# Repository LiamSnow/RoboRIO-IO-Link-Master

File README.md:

# RoboRIO-IO-Link-Master
This repo includes the KiCad project for an 8 port IO-Link master that connects over SPI to the RoboRIO.
For code examples check out [IO-Link C++ Generator](https://github.com/LiamSnow/IO-Link-CPP-Generator) and [Ram Robotics](https://github.com/Ram-Robotics).

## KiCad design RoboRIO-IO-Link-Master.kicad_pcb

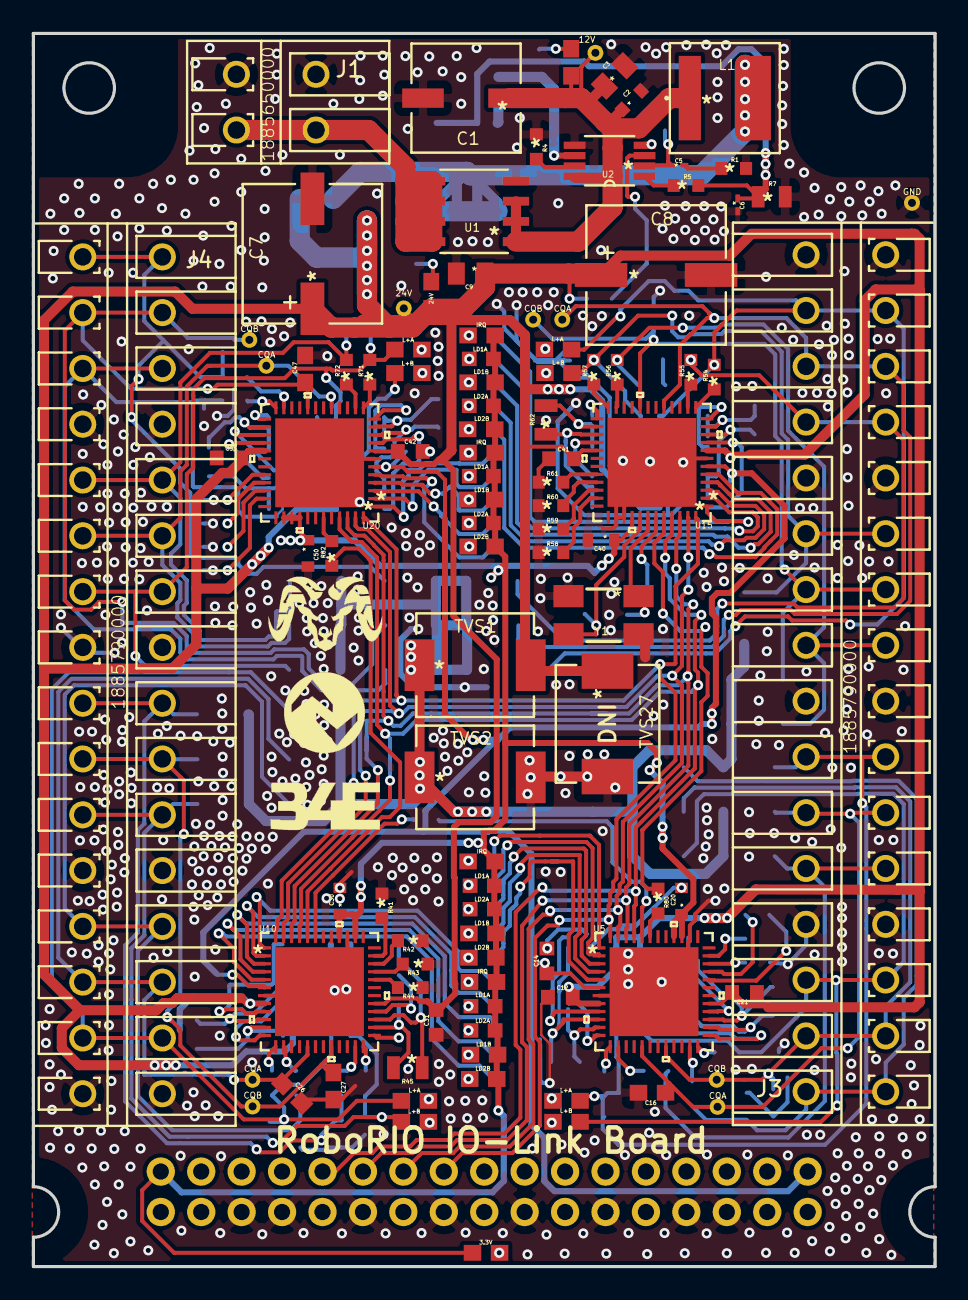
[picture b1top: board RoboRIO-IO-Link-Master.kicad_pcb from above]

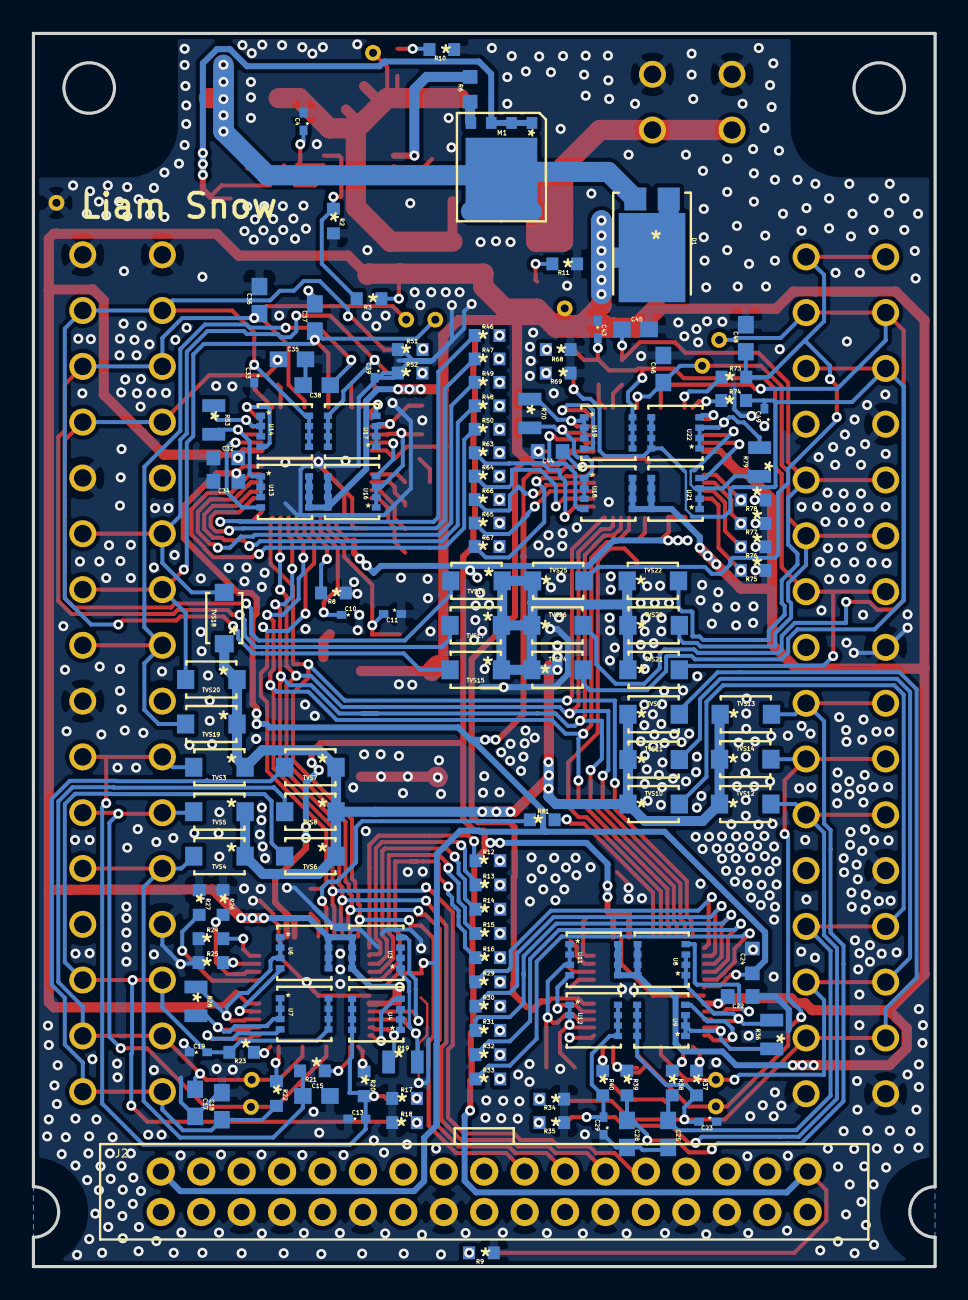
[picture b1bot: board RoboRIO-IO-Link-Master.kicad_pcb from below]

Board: 2 copper layers, 56.6 x 77.5 mm, 232 parts (131 on the bottom side), 168 nets.

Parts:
C1: 100uF-160m; UCL1V101MCL6GS
C2: 100nF-1m; CL10B104KB8NNNC
C3, C9: 10uF; CL21B106KOQNNNE
C4: 1nF; CL05B102KB5NNNC
C5: 22nF; CL03A223KQ3NNNC
C6: 10pF; CL03C100JA3GNNC
C7, C8: 82uF-20m; 35SVPF82M
C10, C11: 5pF; CL05C050CB5NNNC
C12, C14, C21, C22, C24, C31, C32, C34, C41, C42, C44, C51: 1uF; CL10B105MO8NNWC
C13, C19, C23, C29, C33, C39, C43, C49: 0.47uF; CL05A474KP5NNNC
C15, C16, C17, C18, C25, C26, C27, C28, C35, C36, C37, C38, C45, C46, C47, C48: 270pF; CC0603JRNPO9BN271
C20, C30, C40, C50: 0.1uF; CL10B104KB8NNNC
D1: 950mV-10A; FSV10150V
D2: 3.3V; LTSTC191KRKT
D3: 12V; LTSTC191KRKT
D4: 24V; LTSTC191KRKT
D6, D13, D20, D27: IRQ; LTSTC191KFKT
D7, D14, D21, D28: LD1A; LTSTC191TBKT
D8, D15, D22, D29: LD2A; LTSTC191TBKT
D9, D16, D23, D30: LD1B; LTSTC191KGKT
D10, D17, D24, D31: LD2B; LTSTC191KGKT
D11, D18, D25, D32: L+A; LTSTC191KRKT
D12, D19, D26, D33: L+B; LTSTC191KRKT
J1: 1885650000
J2: SFH11-PBPC-D17-ST-BK
J3, J4: 1885790000
L1: 4.7uH-13m; 74439346047
M1: CSD18504Q5A
R1: 4.42k; RC0603FR074K42L
R2, R80, R81, R82: 1k; RC0603FR071KL
R3: 18.2k; RC0603FR0718K2L
R4: 26.1k; RC0603FR0726K1L
R5, R20, R21, R22, R23, R37, R38, R39, R40, R54, R55, R56, R57, R71, R72, R73, R74: 100; RC0603JR07100RL
R6: 0; CRCW06030000Z0EBC
R7: 6m; PMR10EZPFU6L00
R8, R10, R24, R25, R26, R27, R41, R42, R43, R44, R58, R59, R60, R61, R75, R76, R77, R78: 10k; RC0603FR0710KL
R9: 1.5k; RC0603JR071K5L
R11: 22k; RC0603JR0722KL
R12, R13, R14, R15, R16, R29, R30, R31, R32, R33, R46, R47, R48, R49, R50, R63, R64, R65, R66, R67: 820; RC0603FR07820RL
R17, R18, R34, R35, R51, R52, R68, R69: 6.8k; RC0603FR076K8L
R19, R28, R36, R45, R53, R62, R70, R79: .012; KRL1220E-M-R012-F-T5
TP1: GND; TestPointFootprint
TP2: 12V; TestPointFootprint
TP3: 24V; TestPointFootprint
TP7, TP18, TP29, TP40: CQA; TestPointFootprint
TP8, TP19, TP30, TP41: CQB; TestPointFootprint
TVS1: SM30T47AY
TVS2: SM30T35AY
TVS3, TVS4, TVS5, TVS6, TVS7, TVS8, TVS9, TVS10, TVS11, TVS12, TVS13, TVS14, TVS15, TVS16, TVS17, TVS18, TVS19, TVS20, TVS21, TVS22, TVS23, TVS24, TVS25, TVS26: 48V; SMF48A
TVS27: DNI 46.7V; SMCJ40A-TR
U1: SI4431BDY-T1-E3
U2: LM3488MMX_NOPB; LM3488MMX-NOPB
U3, U4, U6, U7, U8, U9, U11, U12, U13, U14, U16, U17, U18, U19, U21, U22: SI7415DN-T1-E3; SI7421DN-T1-E3
U5, U10, U15, U20: MAX14819ATM+; MAX14819ATM&plus_
Y1: ABM3B-14.7456MHZ-10-1-U-T; ABM3B14.7456MHZ101UT

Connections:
+3V3: C20.1, C30.1, C40.1, C50.1, D2.2, D6.2, D7.2, D8.2, D9.2, D10.2, D13.2, D14.2, D15.2, D16.2, D17.2, D20.2, D21.2, D22.2, D23.2, D24.2, D27.2, D28.2, D29.2, D30.2, D31.2, J2.33, U5.39, U5.40, U10.38, U10.40, U15.40, U20.38, U20.39, U20.40
+5V: C14.1, C24.1, C34.1, C44.1, J2.1, U5.6, U10.6, U15.6, U20.6
+12V: C1.1, C2.1, C3.1, D3.2, L1.1, TP2.1, U1.1, U1.2, U1.3, U2.8
+24V: C7.1, C8.1, C9.1, C12.2, C21.2, C22.2, C31.2, C32.2, C41.2, C42.2, C51.2, D1.1, D4.2, R3.1, TP3.1, TVS1.2, TVS27.1, U3.5, U3.6, U3.7, U3.8, U5.8, U5.29, U6.5, U6.6, U6.7, U6.8, U8.5, U8.6, U8.7, U8.8, U10.8, U10.29, U11.5, U11.6, U11.7, U11.8, U13.5, U13.6, U13.7, U13.8, U15.8, U15.29, U16.5, U16.6, U16.7, U16.8, U18.5, U18.6, U18.7, U18.8, U20.8, U20.29, U21.5, U21.6, U21.7, U21.8
/12V: J1.2, U1.5, U1.6, U1.7, U1.8
/DCQ0: C36.1, J3.14, TP29.1, TVS17.2, U15.17
/DCQ1: C37.1, J3.10, TP30.1, TVS20.2, U15.20
/DCQ2: C16.1, J3.6, TP7.1, TVS5.2, U5.17
/DCQ3: C17.1, J3.2, TP8.1, TVS8.2, U5.20
/DCQ4: C26.1, J4.14, TP18.1, TVS11.2, U10.17
/DCQ5: C27.1, J4.10, TP19.1, TVS14.2, U10.20
/DCQ6: C46.1, J4.6, TP40.1, TVS23.2, U20.17
/DCQ7: C47.1, J4.2, TP41.1, TVS26.2, U20.20
/DDI0: C35.1, J3.13, R55.2, TVS16.2
/DDI1: C38.1, J3.9, R56.2, TVS19.2
/DDI2: C15.1, J3.5, R21.2, TVS4.2
/DDI3: C18.1, J3.1, R22.2, TVS7.2
/DDI4: C25.1, J4.13, R38.2, TVS10.2
/DDI5: C28.1, J4.9, R39.2, TVS13.2
/DDI6: C45.1, J4.5, R72.2, TVS22.2
/DDI7: C48.1, J4.1, R73.2, TVS25.2
/DL+0: C33.2, D25.2, J3.15, R54.2, TVS15.2, U14.5, U14.6, U14.7, U14.8
/DL+1: C39.2, D26.2, J3.11, R57.2, TVS18.2, U17.5, U17.6, U17.7, U17.8
/DL+2: C13.2, D11.2, J3.7, R20.2, TVS3.2, U4.5, U4.6, U4.7, U4.8
/DL+3: C19.2, D12.2, J3.3, R23.2, TVS6.2, U7.5, U7.6, U7.7, U7.8
/DL+4: C23.2, D18.2, J4.15, R37.2, TVS9.2, U9.5, U9.6, U9.7, U9.8
/DL+5: C29.2, D19.2, J4.11, R40.2, TVS12.2, U12.5, U12.6, U12.7, U12.8
/DL+6: C43.2, D32.2, J4.7, R71.2, TVS21.2, U19.5, U19.6, U19.7, U19.8
/DL+7: C49.2, D33.2, J4.3, R74.2, TVS24.2, U22.5, U22.6, U22.7, U22.8
/Dual IO-Link Master1/#ERRA-LD2A: R65.1, U20.3
/Dual IO-Link Master1/#ERRB-LD2B: R67.1, U20.5
/Dual IO-Link Master1/#IRQ: R63.1, U20.1
/Dual IO-Link Master1/#RDYA-LD1A: R64.1, U20.2
/Dual IO-Link Master1/#RDYB-LD1B: R66.1, U20.4
/Dual IO-Link Master1/CLKI: R82.2, U20.43
/Dual IO-Link Master2/#ERRA-LD2A: R14.1, U5.3
/Dual IO-Link Master2/#ERRB-LD2B: R16.1, U5.5
/Dual IO-Link Master2/#IRQ: R12.1, U5.1
/Dual IO-Link Master2/#RDYA-LD1A: R13.1, U5.2
/Dual IO-Link Master2/#RDYB-LD1B: R15.1, U5.4
/Dual IO-Link Master2/CLKI: R80.2, U5.43
/Dual IO-Link Master2/CLKO: R81.1, U5.44
/Dual IO-Link Master3/#ERRA-LD2A: R31.1, U10.3
/Dual IO-Link Master3/#ERRB-LD2B: R33.1, U10.5
/Dual IO-Link Master3/#IRQ: R29.1, U10.1
/Dual IO-Link Master3/#RDYA-LD1A: R30.1, U10.2
/Dual IO-Link Master3/#RDYB-LD1B: R32.1, U10.4
/Dual IO-Link Master3/CLKI: R81.2, U10.43
/Dual IO-Link Master3/CLKO: R82.1, U10.44
/Dual IO-Link Master4/#ERRA-LD2A: R48.1, U15.3
/Dual IO-Link Master4/#ERRB-LD2B: R50.1, U15.5
/Dual IO-Link Master4/#IRQ: R46.1, U15.1
/Dual IO-Link Master4/#RDYA-LD1A: R47.1, U15.2
/Dual IO-Link Master4/#RDYB-LD1B: R49.1, U15.4
/Dual IO-Link Master4/CLKI: R8.2, U15.43
/Dual IO-Link Master4/CLKO: R80.1, U15.44
/Dual IO-Link Master4/XI: C11.2, U15.41, Y1.3
/Dual IO-Link Master4/XO: C10.1, U15.42, Y1.1
GND: C1.2, C2.2, C3.2, C4.2, C6.2, C7.2, C8.2, C9.2, C10.2, C11.1, C12.1, C13.1, C14.2, C15.2, C16.2, C17.2, C18.2, C19.1, C20.2, C21.1, C22.1, C23.1, C24.2, C25.2, C26.2, C27.2, C28.2, C29.1, C30.2, C31.1, C32.1, C33.1, C34.2, C35.2, C36.2, C37.2, C38.2, C39.1, C40.2, C41.1, C42.1, C43.1, C44.2, C45.2, C46.2, C47.2, C48.2, C49.1, C50.2, C51.1, J1.1, J2.6, J2.8, J2.12, J2.16, J2.20, J2.24, J2.28, J2.30, J3.4, J3.8, J3.12, J3.16, J4.4, J4.8, J4.12, J4.16, R1.2, R2.2, R4.1, R7.2, R8.1, R9.1, R10.1, R11.1, R17.1, R18.1, R24.1, R25.1, R26.1, R27.1, R34.1, R35.1, R41.1, R42.1, R43.1, R44.1, R51.1, R52.1, R58.1, R59.1, R60.1, R61.1, R68.1, R69.1, R75.1, R76.1, R77.1, R78.1, TP1.1, TVS2.2, TVS27.2, U1.4, U2.4, U2.5, U5.7, U5.38, U5.49, U10.7, U10.39, U10.49, U15.7, U15.38, U15.39, U15.49, U20.7, U20.49, Y1.2, Y1.4
MXP-CS: J2.19, U5.48, U10.48, U15.48, U20.48
MXP-MISO: J2.23, U5.46, U10.46, U15.46, U20.46
MXP-MOSI: J2.25, U5.45, U10.45, U15.45, U20.45
MXP-SCLK: J2.21, U5.47, U10.47, U15.47, U20.47
unnamed: C4.1, C5.1, U2.2
unnamed: C5.2, R1.1
unnamed: C6.1, M1.1, M1.2, M1.3, R5.2, R7.1
unnamed: D1.2, L1.2, M1.5, M1.6, M1.7, M1.8, M1.9
unnamed: D2.1, R9.2
unnamed: D3.1, R10.2
unnamed: D4.1, R11.2
unnamed: D6.1, R12.2
unnamed: D7.1, R13.2
unnamed: D8.1, R14.2
unnamed: D9.1, R15.2
unnamed: D10.1, R16.2
unnamed: D11.1, R17.2
unnamed: D12.1, R18.2
unnamed: D13.1, R29.2
unnamed: D14.1, R30.2
unnamed: D15.1, R31.2
unnamed: D16.1, R32.2
unnamed: D17.1, R33.2
unnamed: D18.1, R34.2
unnamed: D19.1, R35.2
unnamed: D20.1, R46.2
unnamed: D21.1, R47.2
unnamed: D22.1, R48.2
unnamed: D23.1, R49.2
unnamed: D24.1, R50.2
unnamed: D25.1, R51.2
unnamed: D26.1, R52.2
unnamed: D27.1, R63.2
unnamed: D28.1, R64.2
unnamed: D29.1, R65.2
unnamed: D30.1, R66.2
unnamed: D31.1, R67.2
unnamed: D32.1, R68.2
unnamed: D33.1, R69.2
unnamed: M1.4, R6.1
unnamed: R2.1, R3.2, U2.3
unnamed: R4.2, U2.7
unnamed: R5.1, U2.1
unnamed: R6.2, U2.6
unnamed: R19.1, U4.1, U4.2, U4.3, U5.11
unnamed: R19.2, U3.1, U3.2, U3.3, U5.10
unnamed: R20.1, U5.13
unnamed: R21.1, U5.14
unnamed: R22.1, U5.23
unnamed: R23.1, U5.24
unnamed: R24.2, U5.35
unnamed: R25.2, U5.34
unnamed: R26.2, U5.33
unnamed: R27.2, U5.32
unnamed: R28.1, U5.27, U6.1, U6.2, U6.3
unnamed: R28.2, U5.26, U7.1, U7.2, U7.3
unnamed: R36.1, U9.1, U9.2, U9.3, U10.11
unnamed: R36.2, U8.1, U8.2, U8.3, U10.10
unnamed: R37.1, U10.13
unnamed: R38.1, U10.14
unnamed: R39.1, U10.23
unnamed: R40.1, U10.24
unnamed: R41.2, U10.35
unnamed: R42.2, U10.34
unnamed: R43.2, U10.33
unnamed: R44.2, U10.32
unnamed: R45.1, U10.27, U11.1, U11.2, U11.3
unnamed: R45.2, U10.26, U12.1, U12.2, U12.3
unnamed: R53.1, U14.1, U14.2, U14.3, U15.11
unnamed: R53.2, U13.1, U13.2, U13.3, U15.10
unnamed: R54.1, U15.13
unnamed: R55.1, U15.14
unnamed: R56.1, U15.23
unnamed: R57.1, U15.24
unnamed: R58.2, U15.35
unnamed: R59.2, U15.34
unnamed: R60.2, U15.33
unnamed: R61.2, U15.32
unnamed: R62.1, U15.27, U16.1, U16.2, U16.3
unnamed: R62.2, U15.26, U17.1, U17.2, U17.3
unnamed: R70.1, U19.1, U19.2, U19.3, U20.11
unnamed: R70.2, U18.1, U18.2, U18.3, U20.10
unnamed: R71.1, U20.13
unnamed: R72.1, U20.14
unnamed: R73.1, U20.23
unnamed: R74.1, U20.24
unnamed: R75.2, U20.35
unnamed: R76.2, U20.34
unnamed: R77.2, U20.33
unnamed: R78.2, U20.32
unnamed: R79.1, U20.27, U21.1, U21.2, U21.3
unnamed: R79.2, U20.26, U22.1, U22.2, U22.3
unnamed: U3.4, U5.9
unnamed: U4.4, U5.12
unnamed: U5.25, U7.4
unnamed: U5.28, U6.4
unnamed: U8.4, U10.9
unnamed: U9.4, U10.12
unnamed: U10.25, U12.4
unnamed: U10.28, U11.4
unnamed: U13.4, U15.9
unnamed: U14.4, U15.12
unnamed: U15.25, U17.4
unnamed: U15.28, U16.4
unnamed: U18.4, U20.9
unnamed: U19.4, U20.12
unnamed: U20.25, U22.4
unnamed: U20.28, U21.4
TVS_CLAMP: TVS1.1, TVS2.1, TVS3.1, TVS4.1, TVS5.1, TVS6.1, TVS7.1, TVS8.1, TVS9.1, TVS10.1, TVS11.1, TVS12.1, TVS13.1, TVS14.1, TVS15.1, TVS16.1, TVS17.1, TVS18.1, TVS19.1, TVS20.1, TVS21.1, TVS22.1, TVS23.1, TVS24.1, TVS25.1, TVS26.1

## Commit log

2021-04-10 Schematic Work
2021-04-10 New step up that can handle 2A (instead of only 400mA)
2021-04-10 Wrapping up schematics for the MAX14819s
2021-04-13 Schematic edits
2021-04-14 More schematic work
2021-04-14 Imported and Started Footprint Associations
2021-04-18 PCB/Footprint Work
2021-04-19 More PCB Layout
2021-04-22 Wrapping up first prototype
2021-04-23 tweaking

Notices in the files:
parts and their libraries:
Copyright 2016 Accelerated Designs. All rights reserved.
